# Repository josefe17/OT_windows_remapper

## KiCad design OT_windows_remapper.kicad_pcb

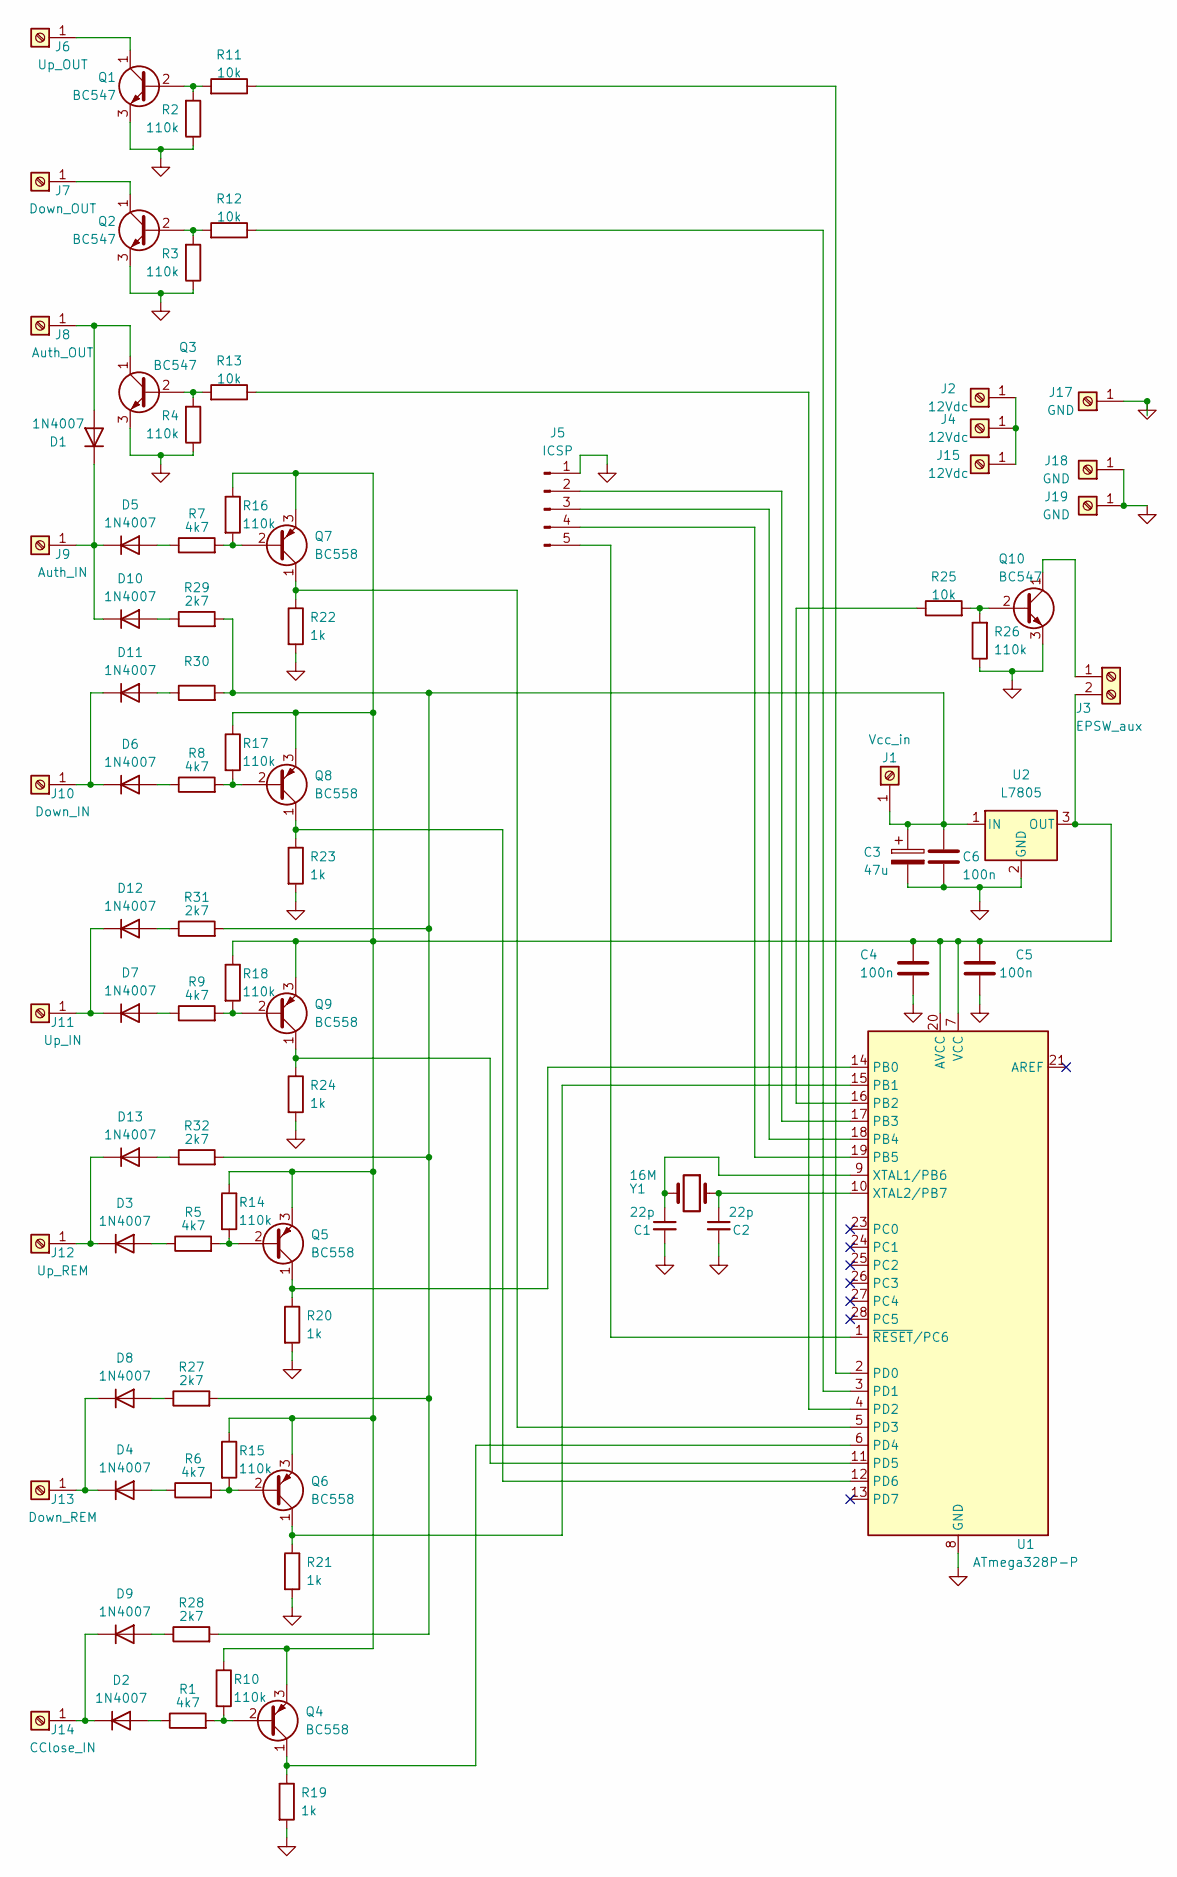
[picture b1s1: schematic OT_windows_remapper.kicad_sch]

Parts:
C1, C2: 22p; C_Disc_D3.0mm_W2.0mm_P2.50mm
C3: 47u; CP_Radial_D8.0mm_P2.50mm
C4, C5, C6: 100n; C_Rect_L7.0mm_W2.5mm_P5.00mm
D1, D2, D3, D4, D5, D6, D7, D8, D9, D10, D11, D12, D13: 1N4007; D_DO-41_SOD81_P2.54mm_Vertical_KathodeUp
J1: Vcc_in; SolderWire-0.75sqmm_1x01_D1.25mm_OD2.3mm
J2, J4, J15: 12Vdc; SolderWire-2sqmm_1x01_D2mm_OD3.9mm
J3: EPSW_aux; SolderWire-0.75sqmm_1x02_P4.8mm_D1.25mm_OD2.3mm
J5: ICSP; PinHeader_1x05_P2.54mm_Vertical
J6: Up_OUT; SolderWire-0.75sqmm_1x01_D1.25mm_OD2.3mm
J7: Down_OUT; SolderWire-0.75sqmm_1x01_D1.25mm_OD2.3mm
J8: Auth_OUT; SolderWire-0.75sqmm_1x01_D1.25mm_OD2.3mm
J9: Auth_IN; SolderWire-0.75sqmm_1x01_D1.25mm_OD2.3mm
J10: Down_IN; SolderWire-0.75sqmm_1x01_D1.25mm_OD2.3mm
J11: Up_IN; SolderWire-0.75sqmm_1x01_D1.25mm_OD2.3mm
J12: Up_REM; SolderWire-0.75sqmm_1x01_D1.25mm_OD2.3mm
J13: Down_REM; SolderWire-0.75sqmm_1x01_D1.25mm_OD2.3mm
J14: CClose_IN; SolderWire-0.75sqmm_1x01_D1.25mm_OD2.3mm
J17: GND; SolderWire-0.75sqmm_1x01_D1.25mm_OD2.3mm
J18, J19: GND; SolderWire-2sqmm_1x01_D2mm_OD3.9mm
Q1, Q2, Q3, Q10: BC547; TO-92_HandSolder
Q4, Q5, Q6, Q7, Q8, Q9: BC558; TO-92_HandSolder
R1, R5, R6, R7, R8, R9: 4k7; R_Axial_DIN0207_L6.3mm_D2.5mm_P2.54mm_Vertical
R2, R3, R4, R10, R14, R15, R16, R17, R18, R26: 110k; R_Axial_DIN0207_L6.3mm_D2.5mm_P2.54mm_Vertical
R11, R12, R13, R25: 10k; R_Axial_DIN0207_L6.3mm_D2.5mm_P2.54mm_Vertical
R19, R20, R21, R22, R23, R24: 1k; R_Axial_DIN0207_L6.3mm_D2.5mm_P2.54mm_Vertical
R27, R28, R29, R31, R32: 2k7; R_Axial_DIN0207_L6.3mm_D2.5mm_P2.54mm_Vertical
R30: R_Axial_DIN0207_L6.3mm_D2.5mm_P2.54mm_Vertical
U1: ATmega328P-P; DIP-28_W7.62mm_Socket_LongPads
U2: L7805; TO-220-3_Vertical
Y1: 16M; Crystal_HC49-U_Vertical

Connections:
GND: C1.2, C2.2, C3.2, C4.2, C5.2, C6.2, J5.1, J17.1, J18.1, J19.1, Q1.3 (E), Q2.3 (E), Q3.3 (E), Q10.3 (E), R2.1, R3.1, R4.1, R19.2, R20.2, R21.2, R22.2, R23.2, R24.2, R26.1, U1.8 (GND), U1.22 (GND), U2.2 (GND)
unnamed: C1.1, U1.9 (XTAL1/PB6), Y1.2
unnamed: C2.1, U1.10 (XTAL2/PB7), Y1.1
unnamed: C3.1, C6.1, J1.1, R27.2, R28.2, R29.2, R30.2, R31.2, R32.2, U2.1 (IN)
unnamed: C4.1, C5.1, J3.2, Q4.3 (E), Q5.3 (E), Q6.3 (E), Q7.3 (E), Q8.3 (E), Q9.3 (E), R10.1, R14.1, R15.1, R16.1, R17.1, R18.1, U1.7 (VCC), U1.20 (AVCC), U2.3 (OUT)
unnamed: D1.1 (K), D5.1 (K), D10.1 (K), J9.1
unnamed: D1.2 (A), J8.1, Q3.1 (C)
unnamed: D2.1 (K), D9.1 (K), J14.1
unnamed: D2.2 (A), R1.1
unnamed: D3.1 (K), D13.1 (K), J12.1
unnamed: D3.2 (A), R5.1
unnamed: D4.1 (K), D8.1 (K), J13.1
unnamed: D4.2 (A), R6.1
unnamed: D5.2 (A), R7.1
unnamed: D6.1 (K), D11.1 (K), J10.1
unnamed: D6.2 (A), R8.1
unnamed: D7.1 (K), D12.1 (K), J11.1
unnamed: D7.2 (A), R9.1
unnamed: D8.2 (A), R27.1
unnamed: D9.2 (A), R28.1
unnamed: D10.2 (A), R29.1
unnamed: D11.2 (A), R30.1
unnamed: D12.2 (A), R31.1
unnamed: D13.2 (A), R32.1
unnamed: J3.1, Q10.1 (C)
unnamed: J5.2, U1.17 (PB3)
unnamed: J5.3, U1.18 (PB4)
unnamed: J5.4, U1.19 (PB5)
unnamed: J5.5, U1.1 (~RESET/PC6)
unnamed: J6.1, Q1.1 (C)
unnamed: J7.1, Q2.1 (C)
unnamed: J2.1, J4.1, J15.1
unnamed: Q1.2 (B), R2.2, R11.2
unnamed: Q2.2 (B), R3.2, R12.2
unnamed: Q3.2 (B), R4.2, R13.2
unnamed: Q4.1 (C), R19.1, U1.6 (PD4)
unnamed: Q4.2 (B), R1.2, R10.2
unnamed: Q5.1 (C), R20.1, U1.14 (PB0)
unnamed: Q5.2 (B), R5.2, R14.2
unnamed: Q6.1 (C), R21.1, U1.15 (PB1)
unnamed: Q6.2 (B), R6.2, R15.2
unnamed: Q7.1 (C), R22.1, U1.5 (PD3)
unnamed: Q7.2 (B), R7.2, R16.2
unnamed: Q8.1 (C), R23.1, U1.12 (PD6)
unnamed: Q8.2 (B), R8.2, R17.2
unnamed: Q9.1 (C), R24.1, U1.11 (PD5)
unnamed: Q9.2 (B), R9.2, R18.2
unnamed: Q10.2 (B), R25.2, R26.2
unnamed: R11.1, U1.2 (PD0)
unnamed: R12.1, U1.3 (PD1)
unnamed: R13.1, U1.4 (PD2)
unnamed: R25.1, U1.16 (PB2)

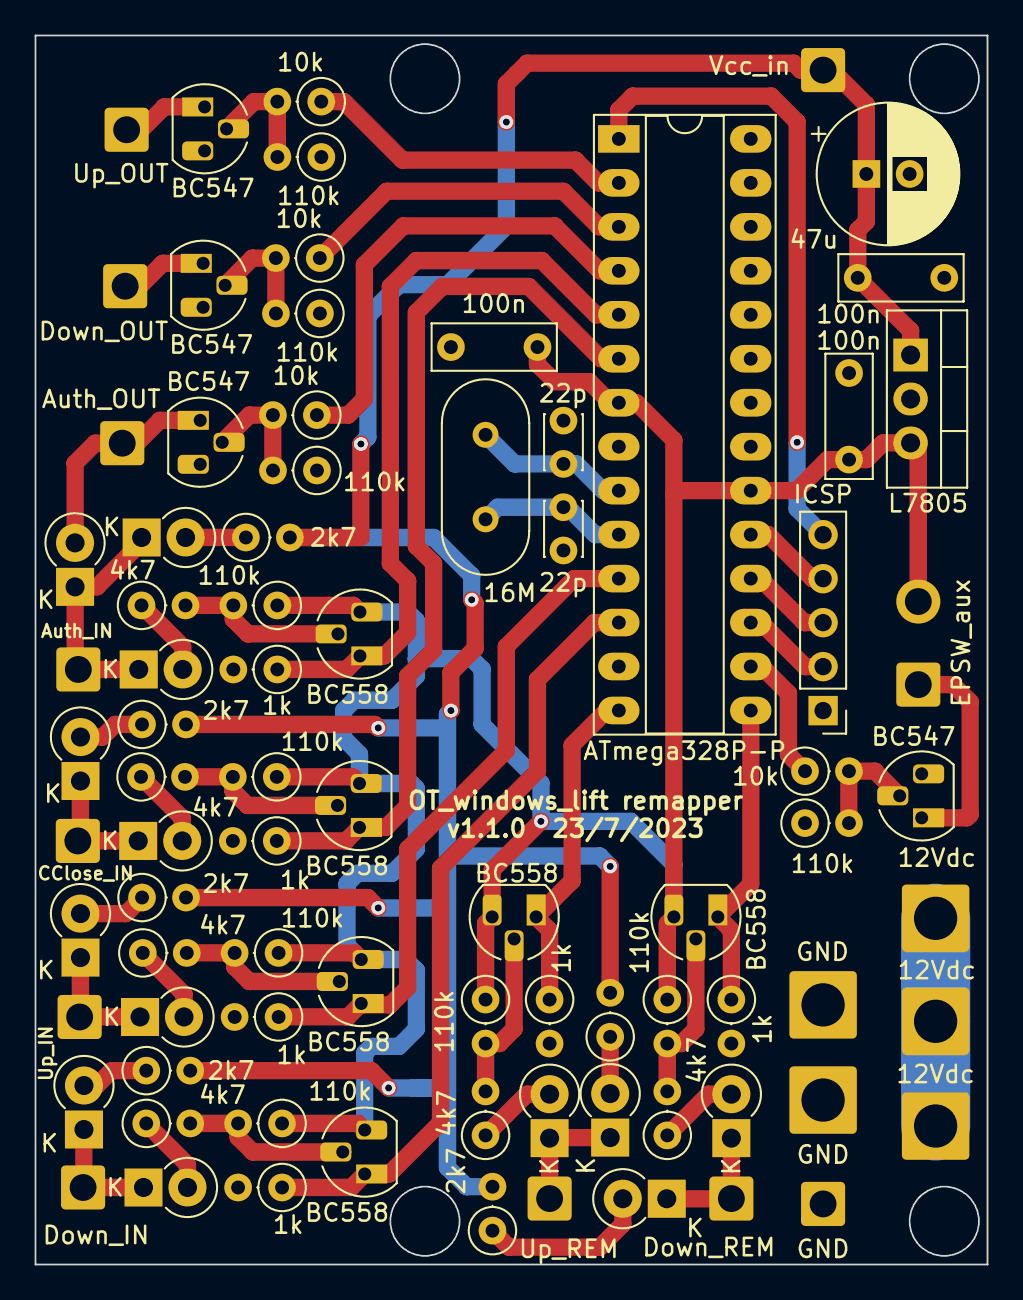
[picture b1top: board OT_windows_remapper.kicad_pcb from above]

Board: 2 copper layers, 55.0 x 71.0 mm, 82 parts (0 on the bottom side), 52 nets.

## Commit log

2023-02-26 Pcb WIP
2023-02-26 First routing
2023-02-28 Silkscreen tidied. Ready to plot.
2023-03-03 plotted v1.0.0 gerbers
2023-07-23 Included 12 V pullups resistors on board
